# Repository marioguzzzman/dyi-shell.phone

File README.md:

# 🐚 DIY Shell Phone

This repository is the open-source reference for the *DYI Shell Phone*, so anyone can build their own, part of **[She Tells, Sea Shells](https://shetells.stream/)**, an artistic research project, developing both an artwork, an installation of the Shetells artwork, and a toolkit. 

The project emerges from the simple, almost childlike gesture of holding a shell to the ear, hearing the ocean’s presence. This toolkit is conceived as a means for the waters of Esposende to exchange with their inhabitants, enabling acts of observation, remembrance, and speculation about the futures of water bodies. Through this, a playful voice is extended to the non-human presences and aquatic landscapes of the ecosystem.

> **Status: work in progress.** The electronics (the custom audio board) are designed and documented here, and the 3D-printable shell is included. Step-by-step assembly guide with photos is being added.

---

## About the project

**English** - The Shellphone is a shell you can listen to. Inside a 3D-printed shell sits a Raspberry Pi Zero 2 W and a small custom audio board. When you hold the shell to your ear, it connects over WiFi to [shetells.stream](https://shetells.stream/) and plays its live **[stream](https://shetells.stream/stream.html)** - a flow of voices and memories that people have shared about water: the sea, rivers, drought, the things we are losing. It turns a familiar gesture - listening to a shell - into a way of listening to each other, and to the water. *(You can also explore the [Living Archive](https://shetells.stream/living-archive.html) to see the memories and the process behind the piece.)*

**Português** - O Shellphone é uma concha que se pode escutar. Dentro de uma concha impressa em 3D estão uma Raspberry Pi Zero 2 W e uma pequena placa de áudio feita à medida. Ao aproximar a concha do ouvido, liga-se por WiFi a [shetells.stream](https://shetells.stream/) e reproduz a sua **[transmissão ao vivo](https://shetells.stream/stream.html)** — um fluxo de vozes e memórias que as pessoas partilharam sobre a água: o mar, os rios, a seca, aquilo que estamos a perder. Transforma um gesto familiar - ouvir uma concha - numa forma de nos ouvirmos uns aos outros, e de ouvir a água. *(Também podes explorar o [Arquivo Vivo](https://shetells.stream/living-archive.html) para ver as memórias e o processo por detrás da peça.)*

---

## How it works

The Shellphone is three parts, hidden inside a shell:

1. **Raspberry Pi Zero 2 W** - a tiny WiFi computer. It connects to the internet and plays the live [stream](https://shetells.stream/stream.html) from [shetells.stream](https://shetells.stream/).
2. **Custom audio board** - a small PCB that plugs onto the Pi like a "HAT". It carries a **MAX98357A I2S amplifier** that turns the Pi's digital audio into a real signal, plus two LED "eyes". The board is shaped like a snail.
3. **Bone-conduction transducer** (8 Ω, 1 W) - instead of a normal speaker, a small transducer that makes whatever it touches vibrate. Mounted against the shell, it turns *the shell itself* into the speaker, so the sound seems to rise out of the shell in your hand.

Everything is powered over USB (5 V).

The audio board connects to the Pi's audio pins like this:

| Amp signal | Raspberry Pi pin |
|---|---|
| Audio clock (BCLK) | GPIO18 (pin 12) |
| Word select (LRC) | GPIO19 (pin 35) |
| Audio data (DIN) | GPIO21 (pin 40) |
| Power (Vin) | 5V (pin 2) |
| Ground (GND) | GND (pin 6) |

*(Full board design: [`hardware/pcb/`](hardware/pcb/), a KiCad project.)*

---

## What's in this repo

| Folder / file | What's inside | Status |
|---|---|---|
| [`hardware/pcb/`](hardware/pcb/) | KiCad design files for the audio board | ✅ Designed |
| [`hardware/bom.md`](hardware/bom.md) | Bill of Materials - the full parts list | ✅ |
| [`enclosure/`](enclosure/) | 3D-printable shell (`.3mf`, `.obj`) | ✅ Included |
| [`images/`](images/) | Photos and board renders | ✅ |
| **Software** | Lives in a **separate repository** (not hosted here) | 🚧 Link coming |
| [`docs/`](docs/) | Assembly guide + build photos | 🚧 Coming |

---

## Build your own

1. **Get the parts** - see the [Bill of Materials](hardware/bom.md).
2. **Make the audio board** - open the KiCad project in [`hardware/pcb/`](hardware/pcb/), export the Gerber files, and send them to any PCB fab (e.g. JLCPCB, PCBWay).
3. **Print the shell** - print the model in [`enclosure/`](enclosure/).
4. **Set up the Raspberry Pi** - flash the SD card and install the streaming software from the [software repository](#software).
5. **Assemble** - solder the board, plug it onto the Pi, attach the bone-conduction transducer to the shell, and fit it all inside. 🚧 *Illustrated guide coming in `docs/`.*

---

## Software

The Raspberry Pi software (connecting to WiFi and playing the stream) lives in its own repository: 🚧 **[link coming soon]**

---

## Credits

Made by:

- **Helin Ulaş** - [helinulas.info](https://helinulas.info/)
- **Rita Eperjesi** - [rita.cloud](https://rita.cloud/)
- **Mario Guzman** - [mario-guzman.com](https://www.mario-guzman.com/)
- **Christian Kokott** - [kokott.art](https://kokott.art/)

Project realised within the framework of the [S+T+ARTS Aqua Motion artistic residency program](https://starts.eu/what-we-do/residences/startsaquamotion/), an initiative co-funded by the European Commission and hosted by [Rio Neiva](https://rioneiva.com/), Esposende, Portugal.

🌐 [shetells.stream](https://shetells.stream/) · 🔊 [Live stream](https://shetells.stream/stream.html) · 📚 [Living Archive](https://shetells.stream/living-archive.html)

<!-- 🚧 TODO: EU-funded acknowledgment line + logo. -->

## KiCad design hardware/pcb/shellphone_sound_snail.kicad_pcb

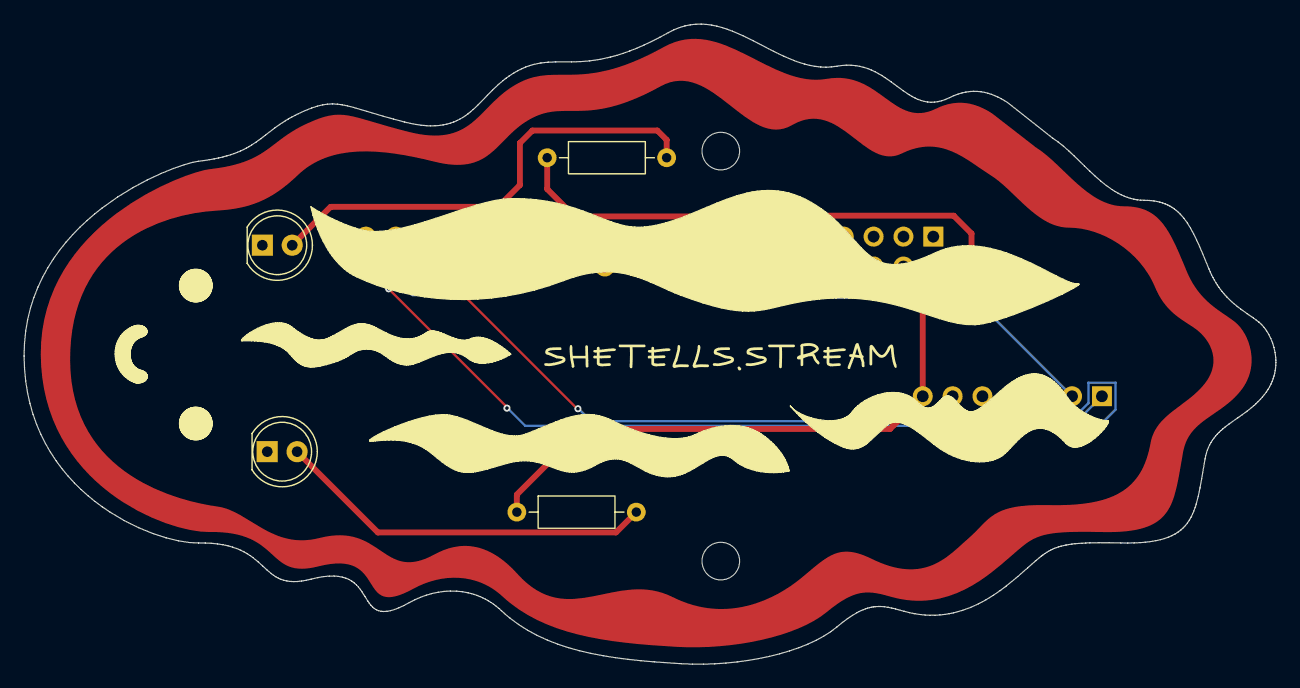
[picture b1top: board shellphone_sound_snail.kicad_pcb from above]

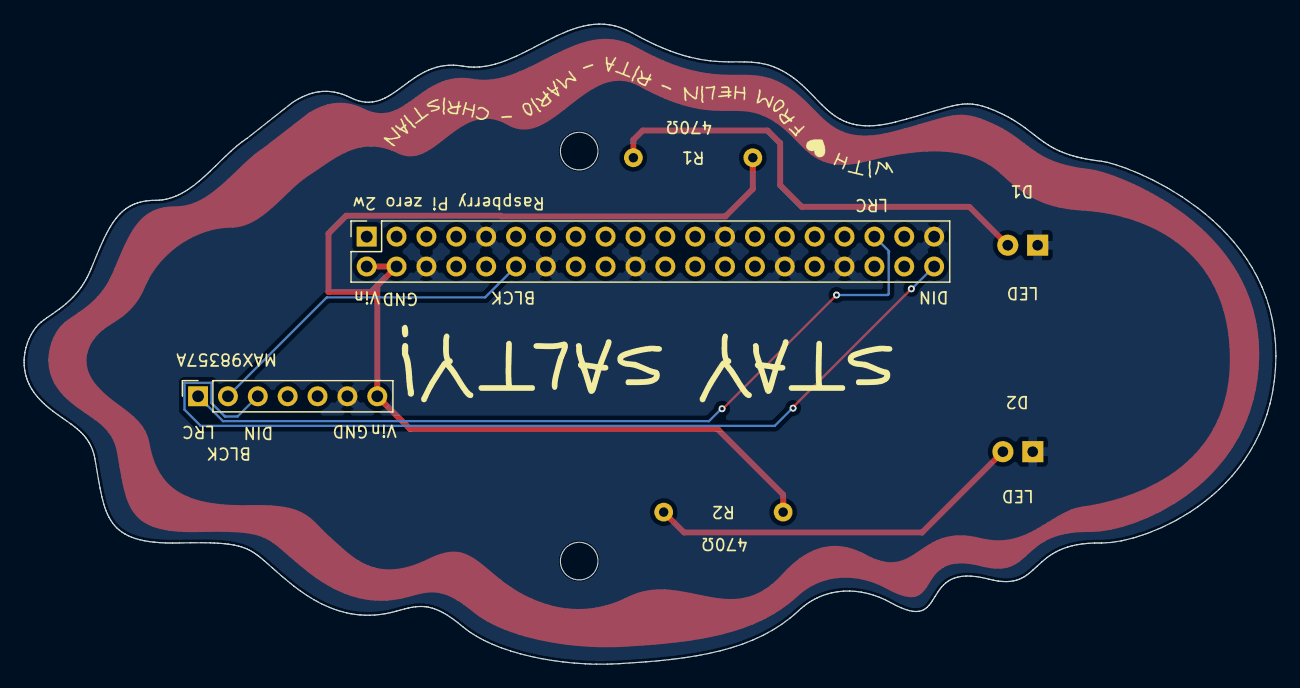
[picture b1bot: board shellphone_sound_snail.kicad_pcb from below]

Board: 2 copper layers, 106.5 x 54.4 mm, 8 parts (2 on the bottom side), 7 nets.

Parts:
D1, D2: LED; LED_D5.0mm
H1, H2: MountingHole; MountingHole_3.2mm_M3_DIN965
J1: Raspberry_Pi_2_3; PinSocket_2x20_P2.54mm_Vertical
J2: MAX98357A; PinSocket_1x07_P2.54mm_Vertical
R1, R2: 470Ω; R_Axial_DIN0207_L6.3mm_D2.5mm_P10.16mm_Horizontal

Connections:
/BCLK: J1.12 (GPIO18/PWM0), J2.2
/DIN: J1.40 (GPIO21/SCLK1), J2.3
/LRC: J1.35 (GPIO19/MISO1), J2.1
/Vin: J1.2 (5V), J1.4 (5V), J2.7, R1.1, R2.1
GND: D1.1 (K), D2.1 (K), J1.6 (GND), J1.9 (GND), J1.14 (GND), J1.20 (GND), J1.25 (GND), J1.30 (GND), J1.34 (GND), J1.39 (GND), J2.6
unnamed: D1.2 (A), R1.2
unnamed: D2.2 (A), R2.2
